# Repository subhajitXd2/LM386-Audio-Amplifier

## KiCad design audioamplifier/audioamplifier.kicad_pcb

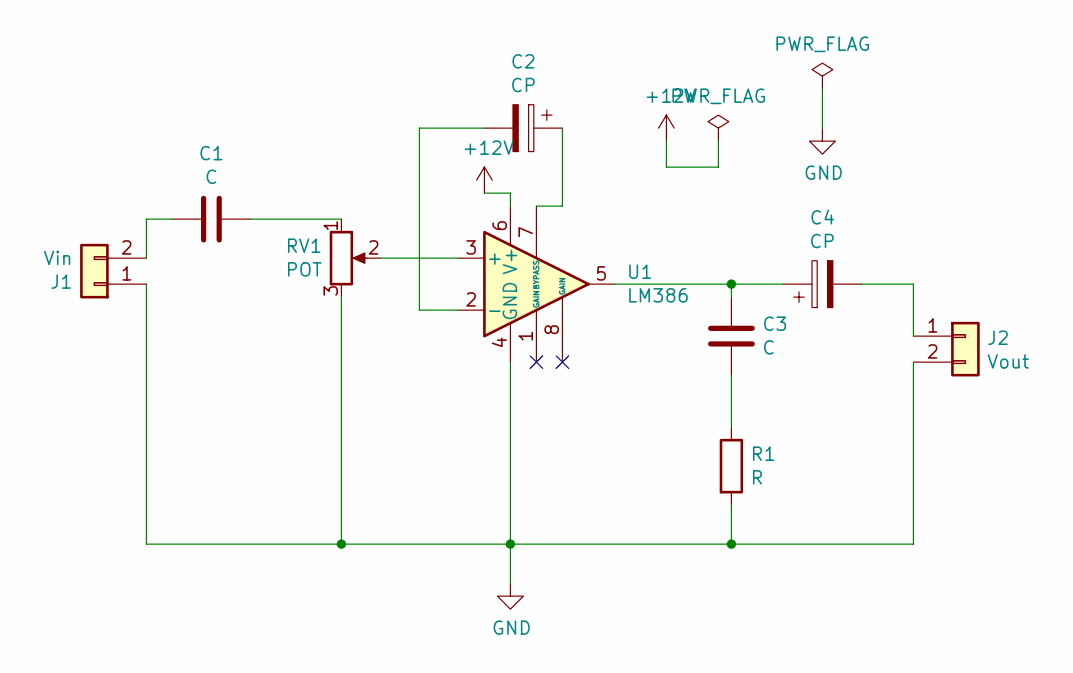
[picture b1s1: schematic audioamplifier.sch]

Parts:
C1, C3: C; C_Disc_D4.3mm_W1.9mm_P5.00mm
C2, C4: CP; CP_Radial_D5.0mm_P2.00mm
J1: Vin; Banana_Jack_2Pin
J2: Vout; Banana_Jack_2Pin
R1: R; R_Axial_DIN0204_L3.6mm_D1.6mm_P7.62mm_Horizontal
RV1: POT; Potentiometer_Bourns_3266X_Horizontal
U1: LM386; Transformer_CHK_EI38-3VA_Neutral

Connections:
+12V: U1.6 (V+)
GND: J1.1, J2.2, R1.2, RV1.3, U1.4 (GND)
unnamed: C1.1, RV1.1
unnamed: C1.2, J1.2
unnamed: C2.1, U1.7 (BYPASS)
unnamed: C2.2, U1.2 (-)
unnamed: C3.1, R1.1
unnamed: C3.2, C4.1, U1.5
unnamed: C4.2, J2.1
unnamed: RV1.2, U1.3 (+)

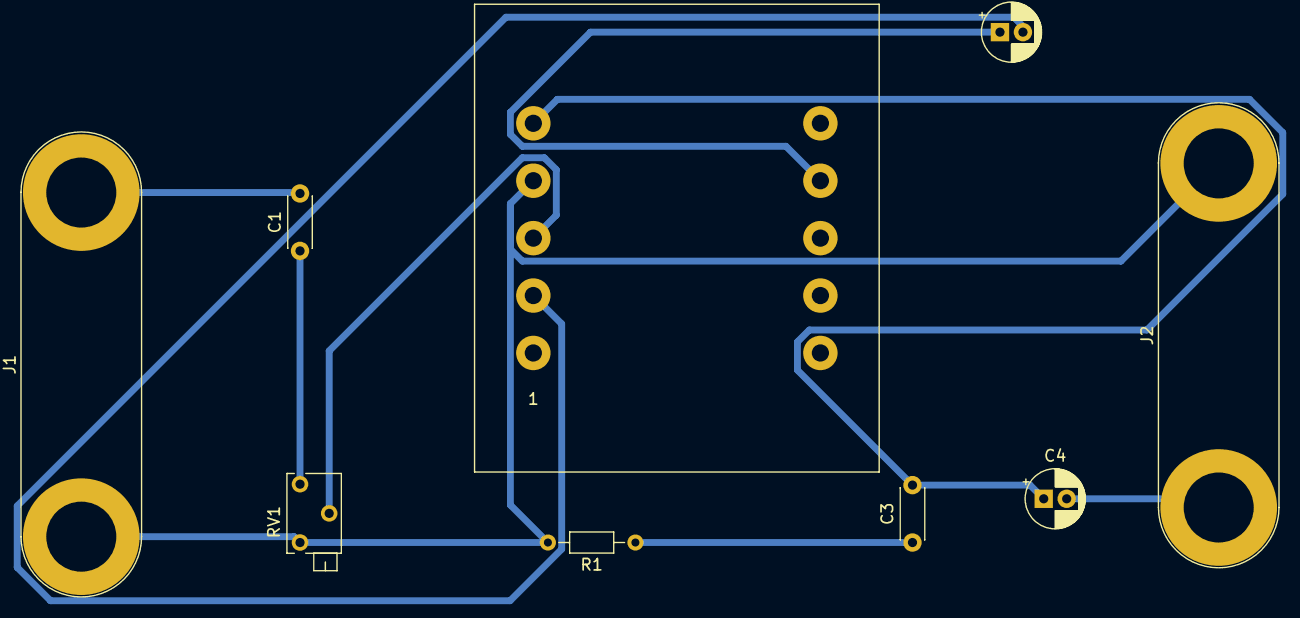
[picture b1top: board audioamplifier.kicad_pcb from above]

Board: 2 copper layers, 9 parts (0 on the bottom side), 9 nets.
